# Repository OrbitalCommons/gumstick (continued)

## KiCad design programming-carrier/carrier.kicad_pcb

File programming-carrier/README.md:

# Module v1 programming and lighting test fixture

This is the **ordered programming-carrier v1**, a USB programmer and slow GPIO
indicator fixture for the ESP32-S2 + iCE40 module. Use the [daughterboard ICD](../current-df40-connectors/docs/ICD-v1.md)
for the interface, [design notes](docs/DESIGN.md) for the circuit, and
[ordered snapshot](releases/v1/README.md) for manufacturing files.

The procedure below specifies a test program to implement. There is **no complete
fixture firmware included here**. Affogato supplies build/loading/SPI building
blocks; [these reviewed setup notes](https://github.com/OrbitalCommons/stratumzero/blob/main/boards/stratumzero/docs/integration/affogato.md)
explain its current capabilities and limitations. The calibrator's GPIO assignments
and bitstream must **not** be used as the fixture test mapping.

## What the LEDs show

There are60 monitored interface signals:27ESP signals (including EN and input-only
GPIO46),30regular FPGA I/O and3FPGA RGB sink outputs. D1/D2 are independent5V and
3V3 TEST indicators. The monitor buffers have both /OE pins tied to ground:
**there is no software bank-enable signal**. “One bank at a time” means drive
only that bank's eligible GPIOs active while driving other eligible outputs inactive.

Green signal LEDs indicate HIGH. Red RGB monitor LEDs indicate LOW. Each monitor
has its own resistor and buffer; the GPIO drives a high-impedance input with100k
bias, not the LED current. An LED being lit proves an observed logic level,
not rated drive strength or a complete input-path/analog/high-speed test.

Use [led-map.json](docs/led-map.json) as the machine-readable test list. Group by
`buffer`, preserve `input` order, and carry `active_low`; do not assume consecutive
LED reference numbers cover every footprint or that a GPIO suffix is a FPGA pad.
The [ICD CSV](../current-df40-connectors/docs/icd-v1-pinout.csv) maps each FPGA net to
its physical package pin for the fixture PCF.

## Setup and recovery

1. Unplug USB before fitting/removing the module. Seat both complementary DF40
   connectors evenly and use the2mm spacer/M3 retention without forcing engagement.
2. Connect a data-capable USB cable to an adequately powered, current-limited
   source/hub. This fixture uses USB CC resistors and a500mA-hold fuse; it has
   **no PD negotiation**. Fuse rating is not an authorization to draw arbitrary
   USB current. Start Wi-Fi off and a sparse LED pattern; measure total current.
3. For first flash: SW1=BOOT, press/release SW2 RESET, use native ESP32-S2 USB
   ROM programming, then SW1=RUN and RESET. Release SW3(GPIO46) during reset.
4. Use USB CDC for logs and commands. Disable UART logging/peripherals on43/44
   when testing those pins. Check FPGA loader CDONE and runtime identification.
5. Program distinct firmware identity `programming-carrier-v1-test` and require
   explicit operator arming after boot. This board has no electronic carrier-ID
   interlock: the operator must confirm the fixture. Running this sweep on the
   calibrator would toggle regulator enables, I²C and GPS pins as arbitrary LEDs.

## Pin classes: do not blindly sweep everything

| Signal | Treatment |
|---|---|
| ESP_EN / D10 | Observe high during normal run; SW2 reset tests it. Never use as a normal firmware output |
| GPIO0 / D11 | Keep high/input normally; SW1 controls BOOT/RUN. Exclude from automated bank/walk tests |
| GPIO46 / D36 | **Input only**; use SW3 after boot, read low released/high pressed. Never set output mode |
| GPIO45 / D35 | Flash-voltage strap. Keep low/high-Z through reset; optional separate post-boot test only, then return low before reset |
| ESP GPIO1–8,15–18,21,33–35,38–44 | Ordinary fixture outputs after disabling other peripheral owners |
| ESP GPIO9–14,36,37 | Internal FPGA link/reset/CDONE; not part of indicator sweep |
| ESP GPIO19/20 | USB; never repurpose during USB testing |
| FPGA ordinary30GPIOs | Output test via dedicated FPGA test design, physical pins from ICD |
| FPGA RGB0/1/2 | Current-sink outputs shared with module RGB LED; separate RGB-driver test |

Normal EN and GPIO0 indicators may remain lit while the eligible outputs are
blank. The power indicators also stay on. Log this exception so a technician
does not misdiagnose “all off.” GPIO45's special test should be opt-in; an MCU
reset while a strap is driven high deserves explicit hardware validation.
Do not change eFuses or flash-voltage settings to make a lighting test pass.

## Suggested program structure

- ESP task owns a bank/pin table generated from `led-map.json`, a USB command
  parser, a nonblocking pattern scheduler and a result log.
- A small FPGA fixture image exposes a30-bit regular-output mask, three RGB
  controls, readback/identity and a heartbeat/watchdog. It can use HFOSC; no
  external OCXO is fitted on this carrier.
- Use a tested, versioned SPI transport to apply FPGA masks atomically; do not
  assume Affogato's example register map already implements these controls.
- On boot/fault/timeout: regular test outputs low, RGB current sinks disabled,
  GPIO0 left safe, GPIO45low, GPIO46input. Require explicit `start` to illuminate.
- For RGB, use `SB_RGBA_DRV` with a conservative supported current and individual
  PWM controls. “Off” releases the sink, allowing the fixture100k pull-up to turn
  off its red LED. “On” sinks the line low; both module and monitor response should
  be inspected. Do not drive the shared sink pins as push-pull HIGH outputs.

Pseudocode (conceptual API, not an implemented library):

```text
safe_start()
verify_fpga_abi()
wait_for_operator_fixture_confirmation()

for bank in regular_banks_in_physical_order:
    eligible_outputs_off()                # EN/BOOT indicators are exceptions
    set_bank_mask(bank, eligible_mask)    # only post-boot safe push-pull pins
    wait_nonblocking(1000 ms)
    record_operator_result(bank)
    eligible_outputs_off()
    wait_nonblocking(300 ms)

for bank in regular_banks_in_physical_order:
    for channel in bank.eligible_channels:
        eligible_outputs_off()
        channel_set(channel, ON)
        log_expected_led_and_signal(channel)
        wait_nonblocking(300 ms)
        channel_set(channel, OFF)
        wait_nonblocking(150 ms)

run_checkerboards_one_bank_at_a_time()
run_walking_zero_one_bank_at_a_time()
run_short_all_regular_on_test_if_power_budget_allows()
run_rgb_sink_test_separately()
run_manual_boot_reset_and_gpio46_checks()
eligible_outputs_off()
```

For the human-visible sequence use300–1000ms dwell, not high-frequency PWM.
Offer pause/step/hold/repeat/reverse so a suspect solder joint can be probed.
A camera/photodiode can automate observation later; GPIO register readback alone
cannot confirm that the LED, buffer or connector contact actually works.

## Test phases and expected observations

1. **Baseline:** D1/D2 power, EN and RUN/BOOT indicators as described; all other
   driven regular outputs low and RGB released. Note any stuck-on lamps.
2. **One bank at a time:** light all eligible pins in U3, then U4…U10, with other
   eligible banks off. Verify location, uniformity and no unintended neighboring
   bank. U3/U6 have restricted pins; their whole physical bank will not light.
3. **Walking one:** one eligible green lamp at a time in table order, then reverse.
   Every transition is logged with signal, LED reference, connector and package
   pin. Look for missing, mirrored, duplicated and neighboring lights.
4. **Alternating:** even then odd eligible channels (`0x55` /`0xAA` masked to actual
   channels). Alternate at~2Hz. This can expose shorts masked by an all-on pattern.
5. **Walking zero:** selected bank on except one eligible channel off; other banks
   remain off. This catches stuck-high and pairwise bridge behavior.
6. **Cross-bank/all-on:** brief simultaneous regular-output test after current and
   regulator-temperature checks. The3.3V LDO and USB budget must tolerate it; the
   presence of buffers does not remove the electrical load. Limit dwell initially.
7. **RGB:** individually enable RGB0,RGB1,RGB2 sinks, then combinations. Red monitor
   polarity is inverted; inspect the module RGB LED too. Return all sinks off.
8. **Inputs/control:** press/releaseGPIO46 button after boot and log reads; verify
   EN/reset and BOOT/RUN via the physical controls in a separate controlled step.
9. **Optional input coverage:** place one ordinary pin in input mode, then apply a
   known0/3.3V through a series resistor to its accessible signal-side bias-resistor
   pad; read it back. Never drive against an output or use5V. This is separate from
   the output lamp test and requires deliberate external stimulus.

Proposed USB commands to implement: `fixture status`, `fixture banks`,
`fixture bank U7`, `fixture walk`, `fixture step`, `fixture hold FPGA_IOB_3B_G6`,
`fixture checkerboard`, `fixture rgb 1`, `fixture input46`, `fixture stop`.
`stop` must work during every dwell; use task timers/state transitions, not a
blocking multi-minute loop. Reset should return to idle, never auto-repeat all-on.

## Test report and coverage limits

Save module serial/operator ID, module/interface revision, app/FPGA hashes,
measured USB voltage/current, selected dwell, expected/observed result for each
channel, optional photos and faults. Distinguish **command applied**, **pin readback**,
and **optically observed**; only the last establishes a visible lamp result.

This fixture does not validate RF performance, high-speed signal integrity,
FPGA global clock routing, ADC precision, full current capability or every input
path. It loads signals with long traces/buffer inputs and is intended for slow
functional tests. Finish with outputs safe, SW1 RUN, and OTA/recovery firmware
validated before installing the module on an application carrier.

## Physical bank/channel order

The table below is generated from `docs/led-map.json` for the ordered fixture.
D37–D41 and D72–D73 are not populated channels in this map; do not fill numeric gaps.

| Buffer | Kind | Channels in input-pin order |
|---|---|---|
| U3 | ESP | D10=EN; D11=GPIO0_BOOT; D12=GPIO1; D13=GPIO2; D14=GPIO3; D15=GPIO4; D16=GPIO5; D17=GPIO6 |
| U4 | ESP | D18=GPIO7; D19=GPIO8; D20=GPIO15; D21=GPIO16; D22=GPIO17; D23=GPIO18; D24=GPIO21; D25=GPIO33 |
| U5 | ESP | D26=GPIO34; D27=GPIO35; D28=GPIO38; D29=GPIO39; D30=GPIO40; D31=GPIO41; D32=GPIO42; D33=GPIO43_TXD |
| U6 | ESP | D34=GPIO44_RXD; D35=GPIO45; D36=GPIO46 |
| U7 | FPGA | D42=IOB_0A; D43=IOB_2A; D44=IOB_3B_G6; D45=IOB_4A; D46=IOB_5B; D47=IOB_6A; D48=IOB_8A; D49=IOB_9B |
| U8 | FPGA | D50=IOB_13B; D51=IOB_16A; D52=IOB_18A; D53=IOB_20A; D54=IOB_22A; D55=IOB_23B; D56=IOB_25B_G3; D57=IOB_29B |
| U9 | FPGA | D58=IOT_36B; D59=IOT_37A; D60=IOT_38B; D61=IOT_39A; D62=IOT_41A; D63=IOT_42B; D64=IOT_43A; D65=IOT_44B |
| U10 | FPGA | D66=IOT_45A_G1; D67=IOT_46B_G0; D68=IOT_48B; D69=IOT_49A; D70=IOT_50B; D71=IOT_51A |
| U11 | RGB | D74=RGB0; D75=RGB1; D76=RGB2 |

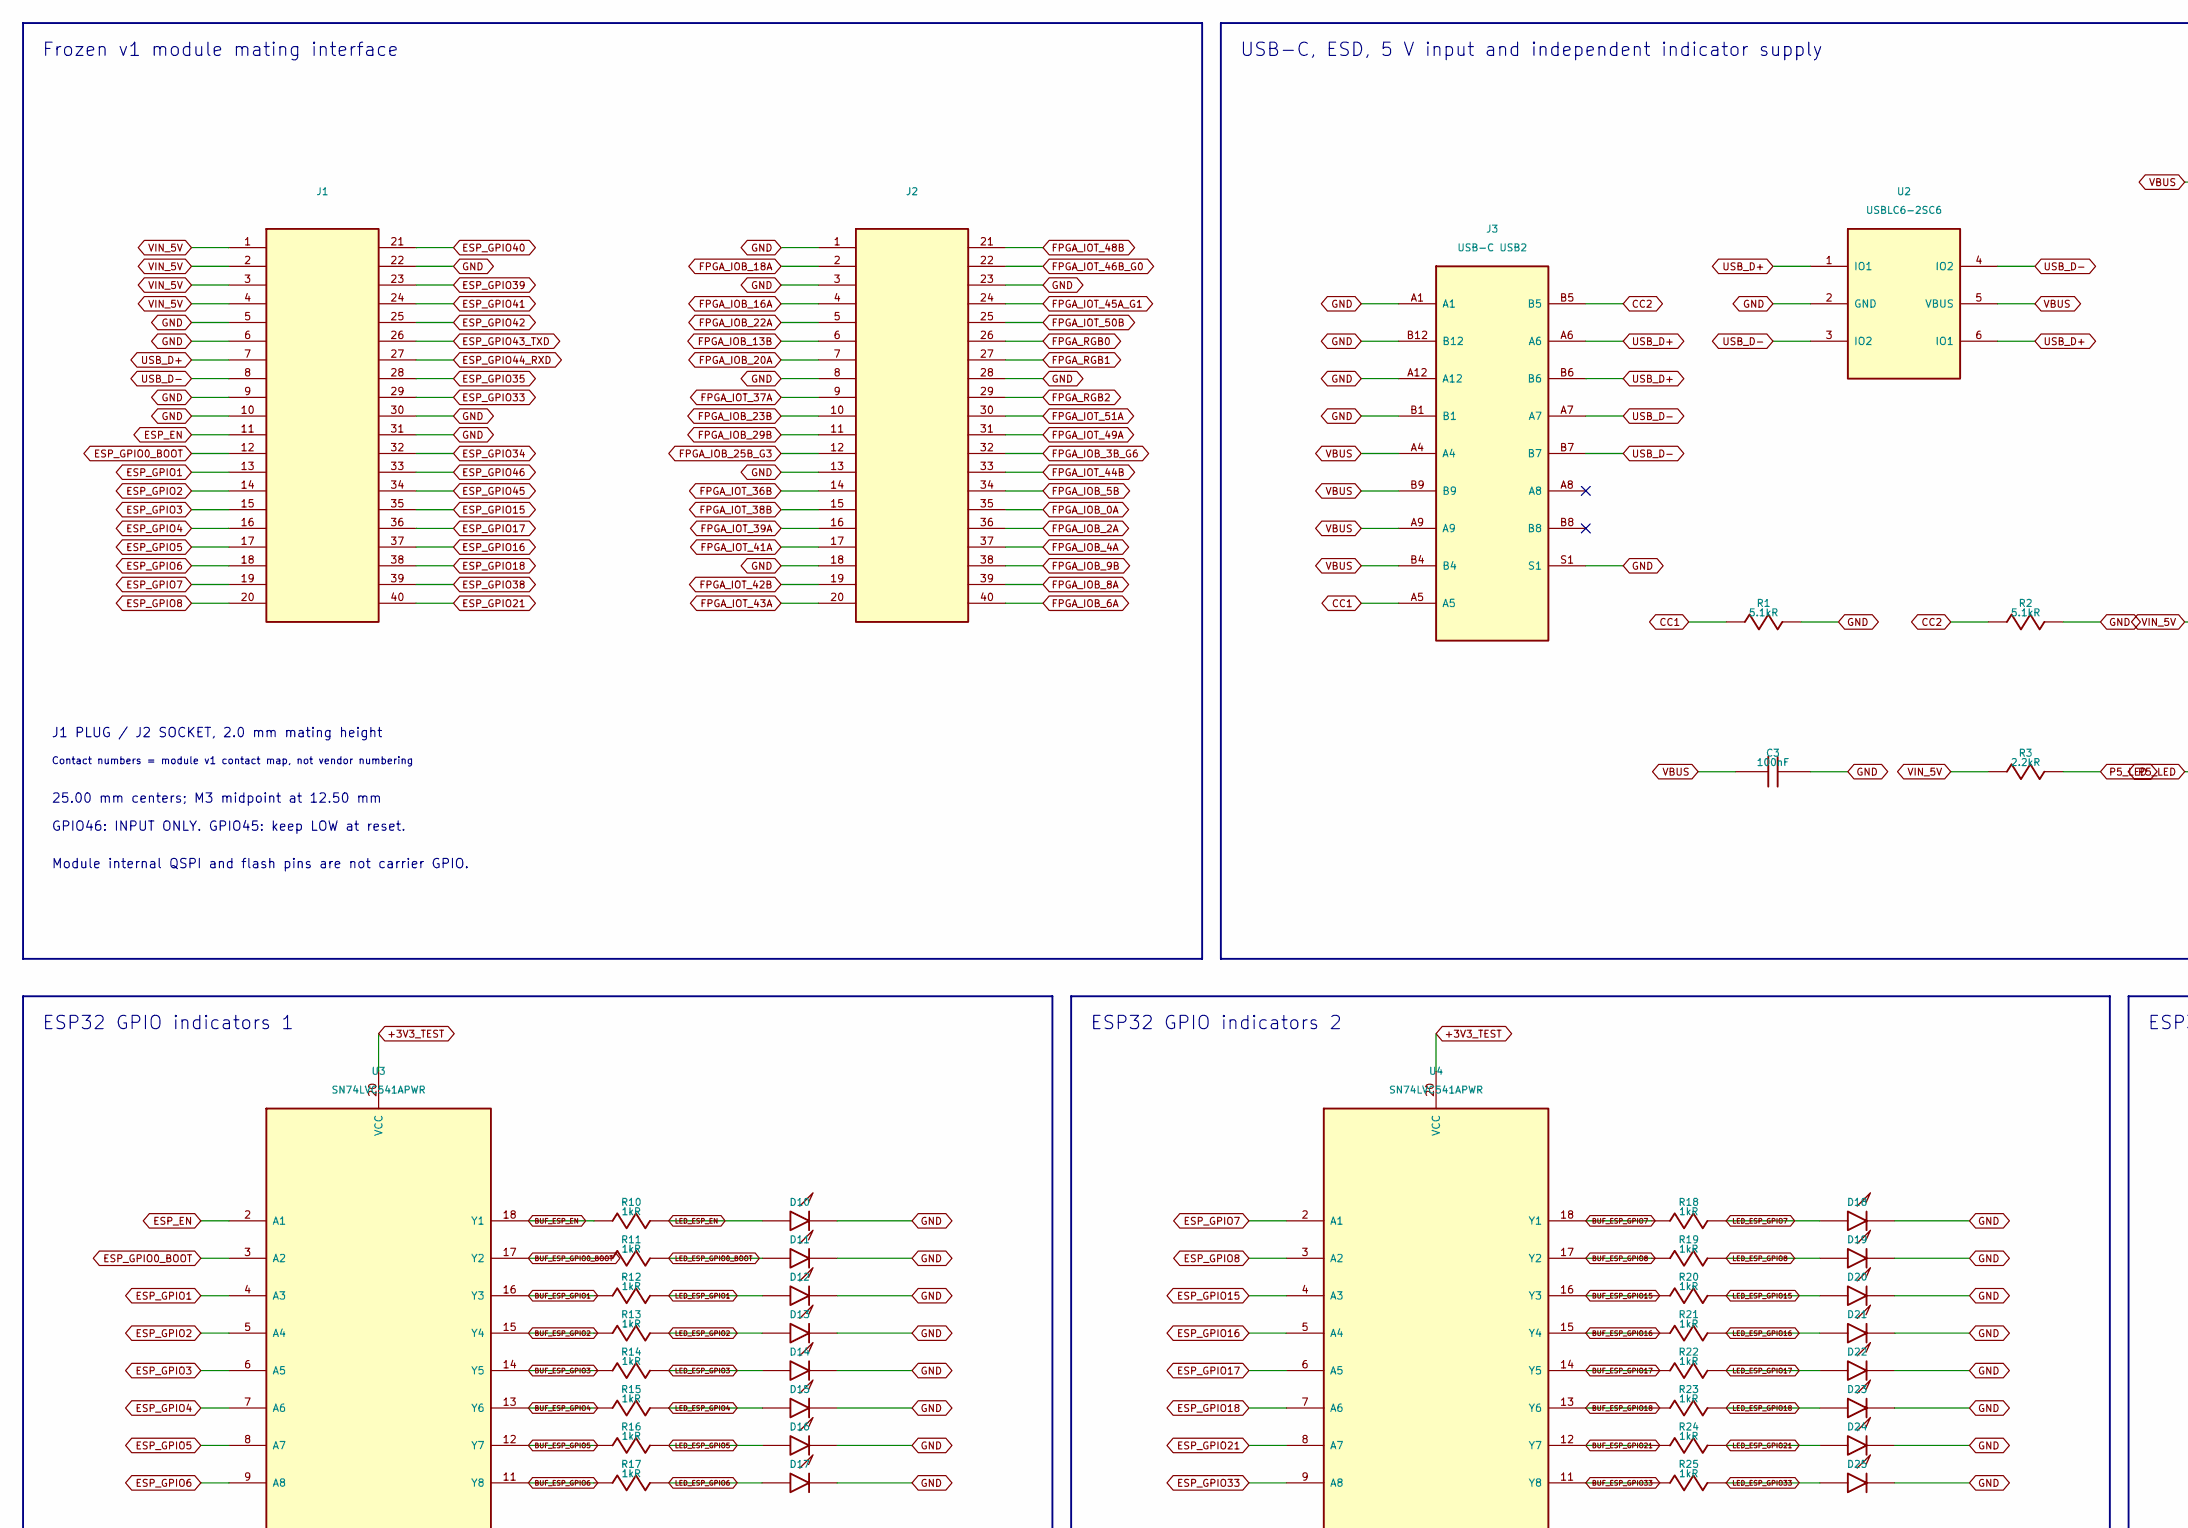
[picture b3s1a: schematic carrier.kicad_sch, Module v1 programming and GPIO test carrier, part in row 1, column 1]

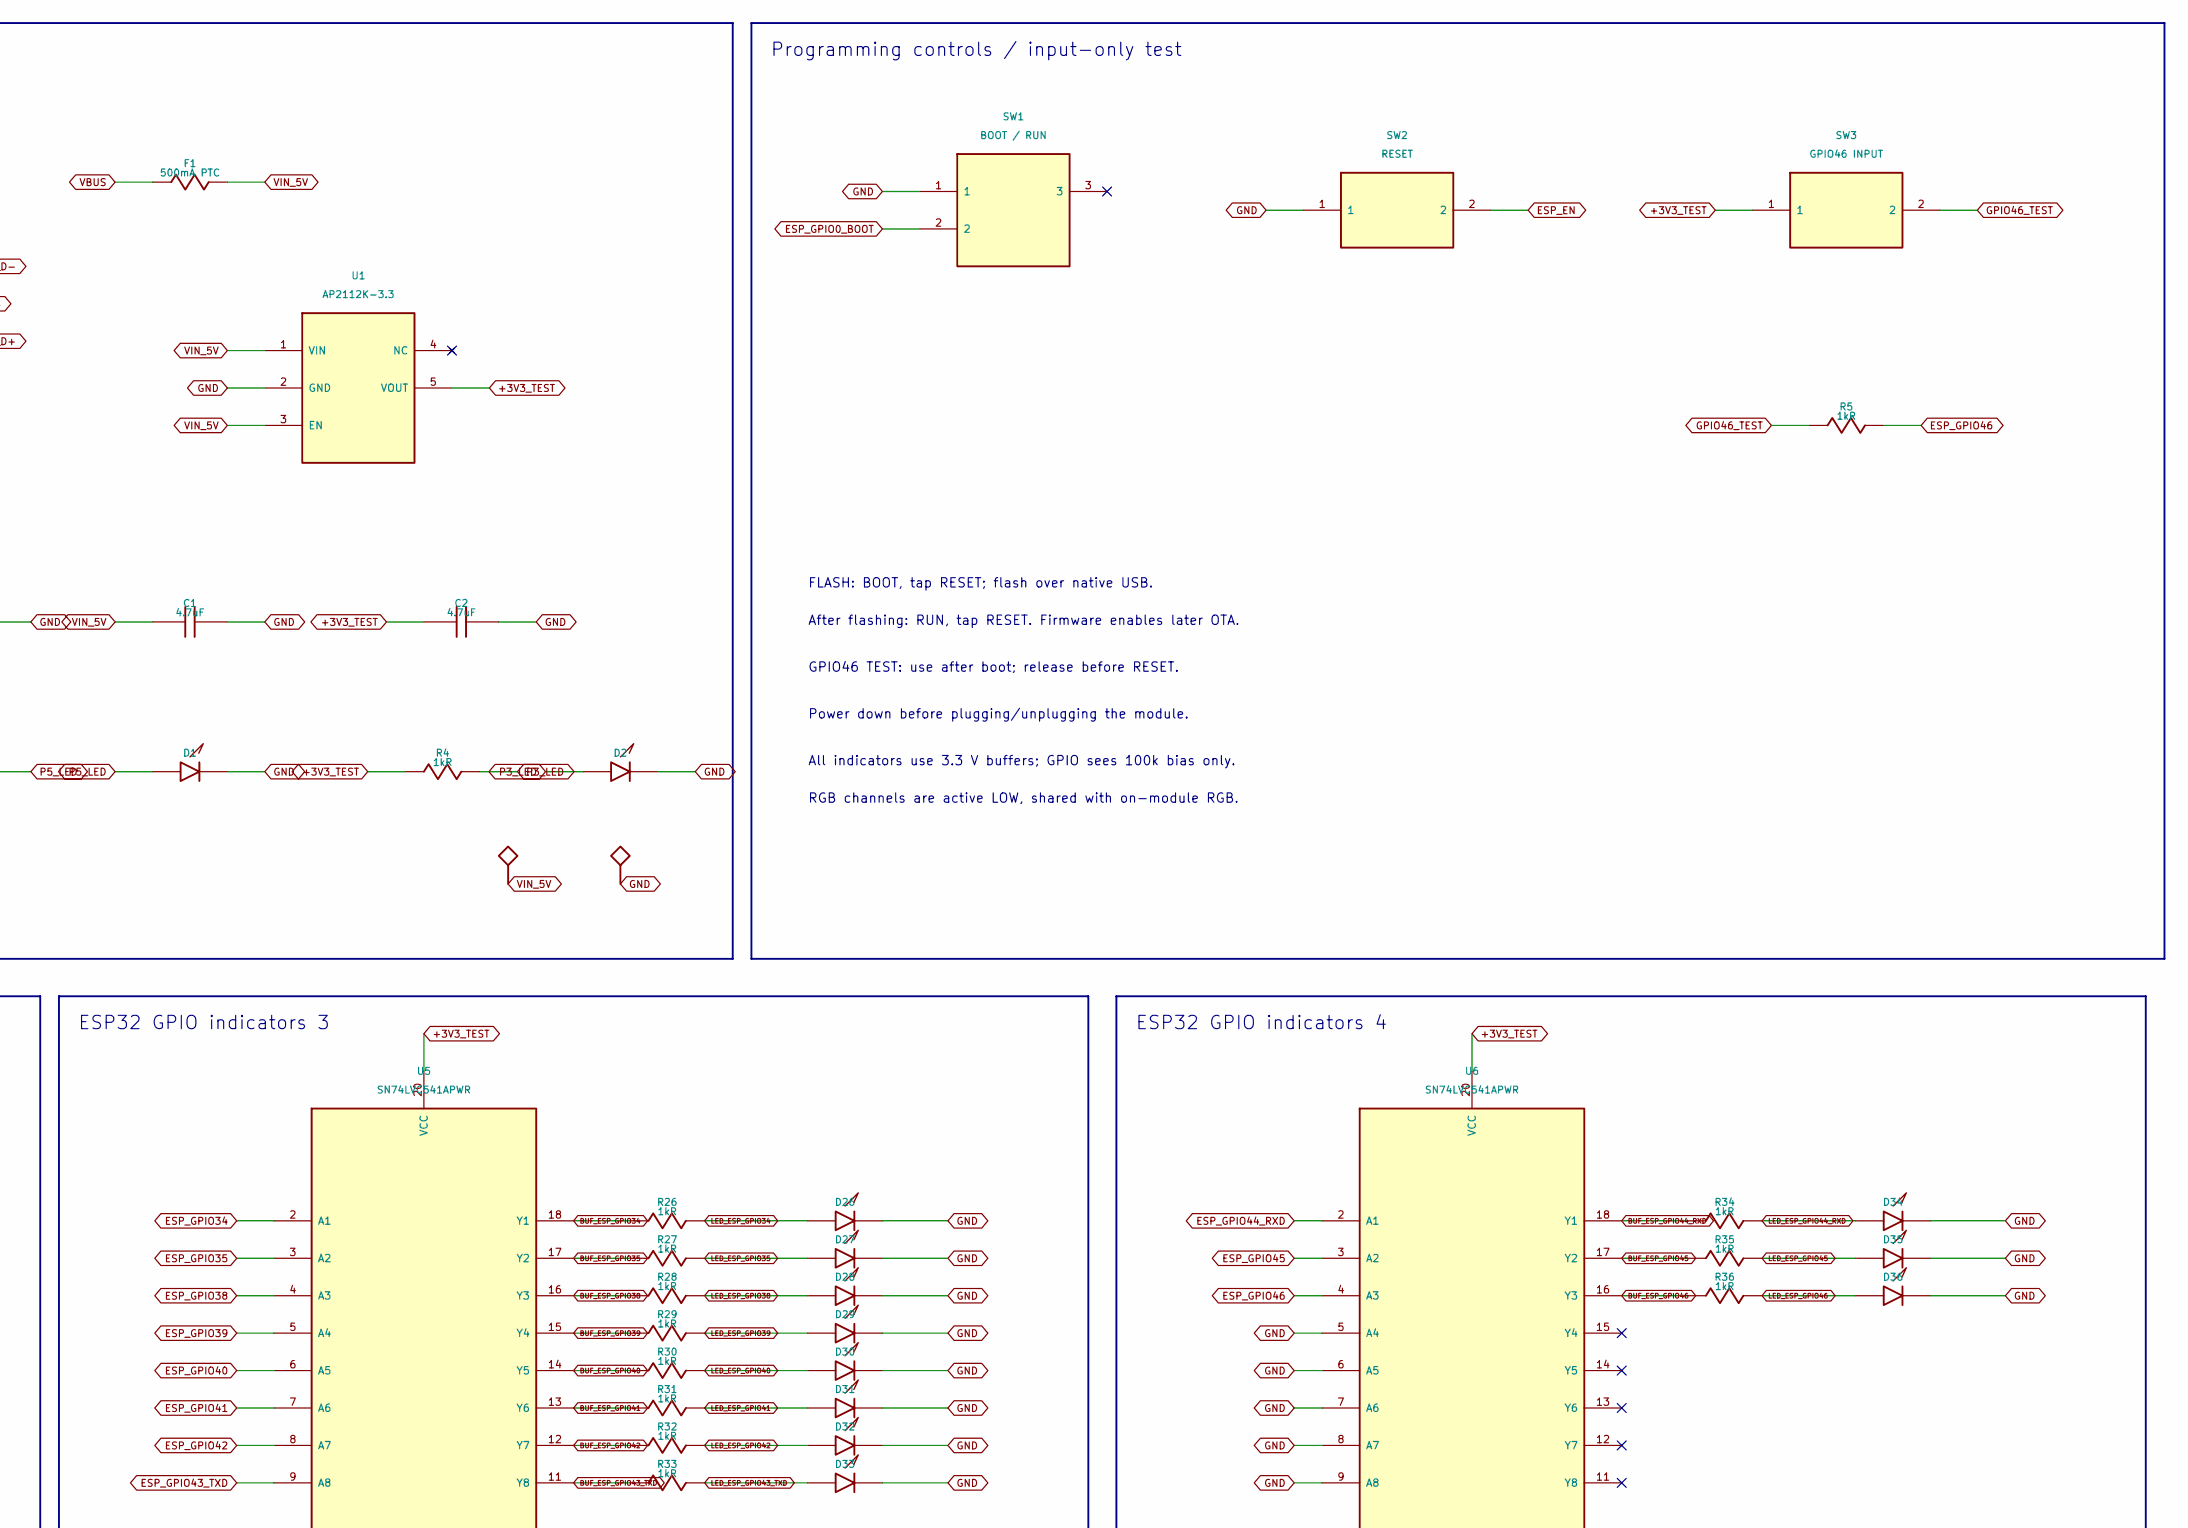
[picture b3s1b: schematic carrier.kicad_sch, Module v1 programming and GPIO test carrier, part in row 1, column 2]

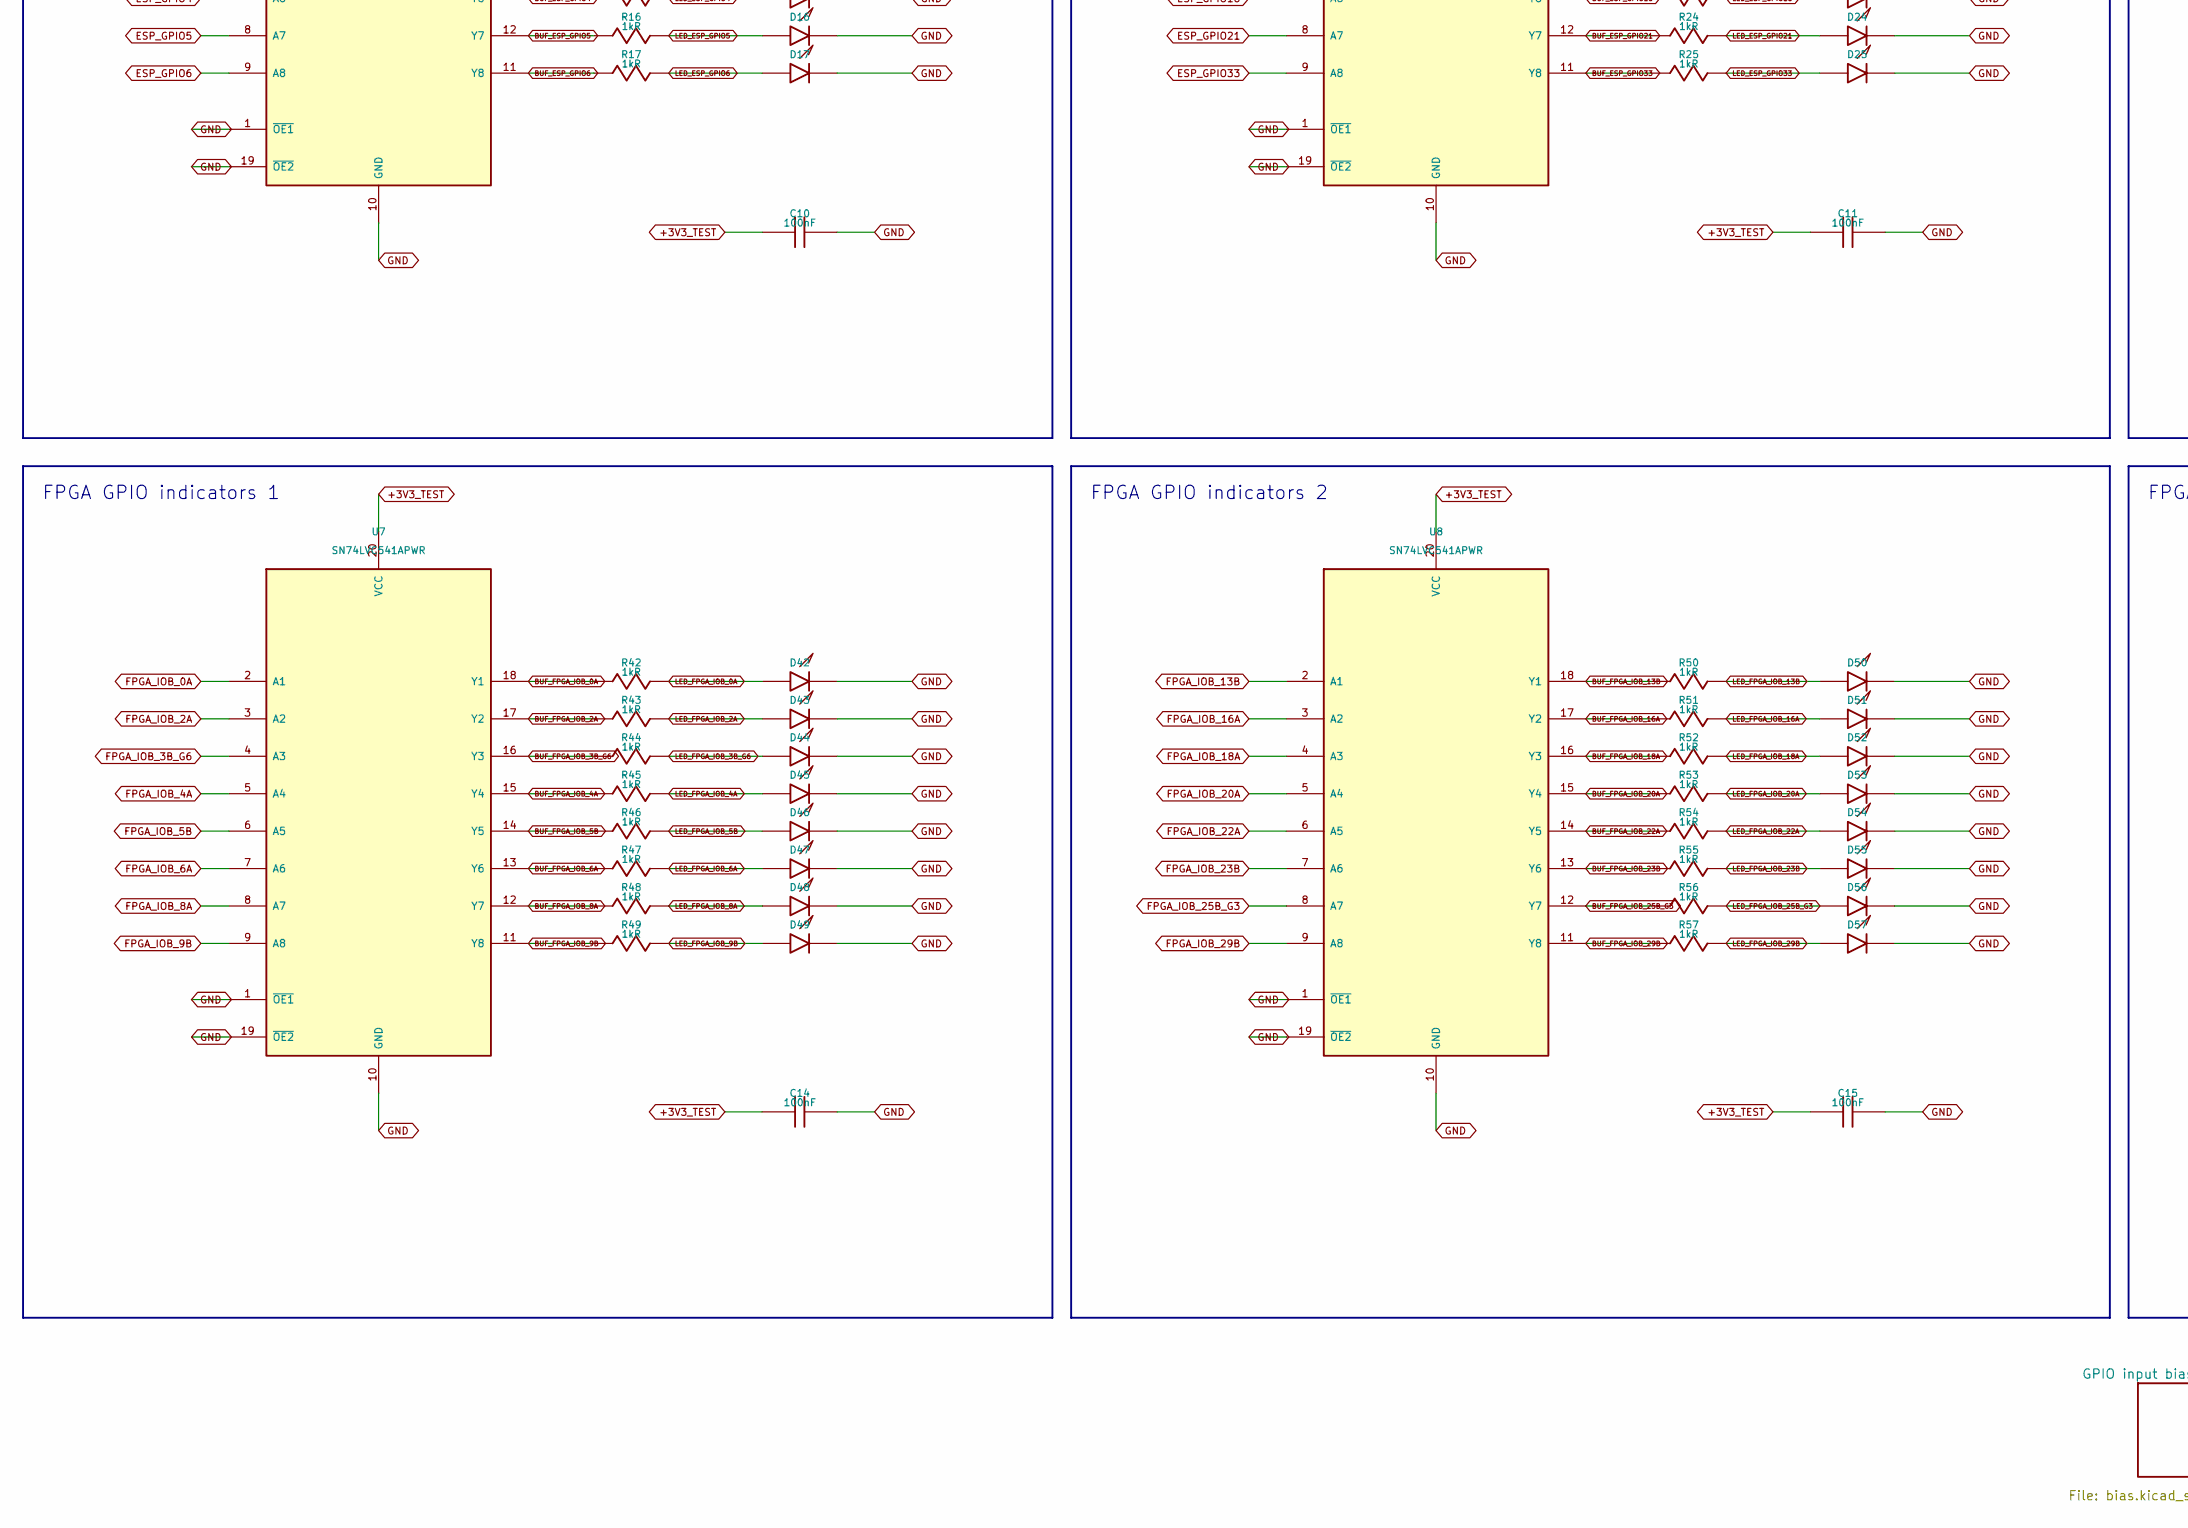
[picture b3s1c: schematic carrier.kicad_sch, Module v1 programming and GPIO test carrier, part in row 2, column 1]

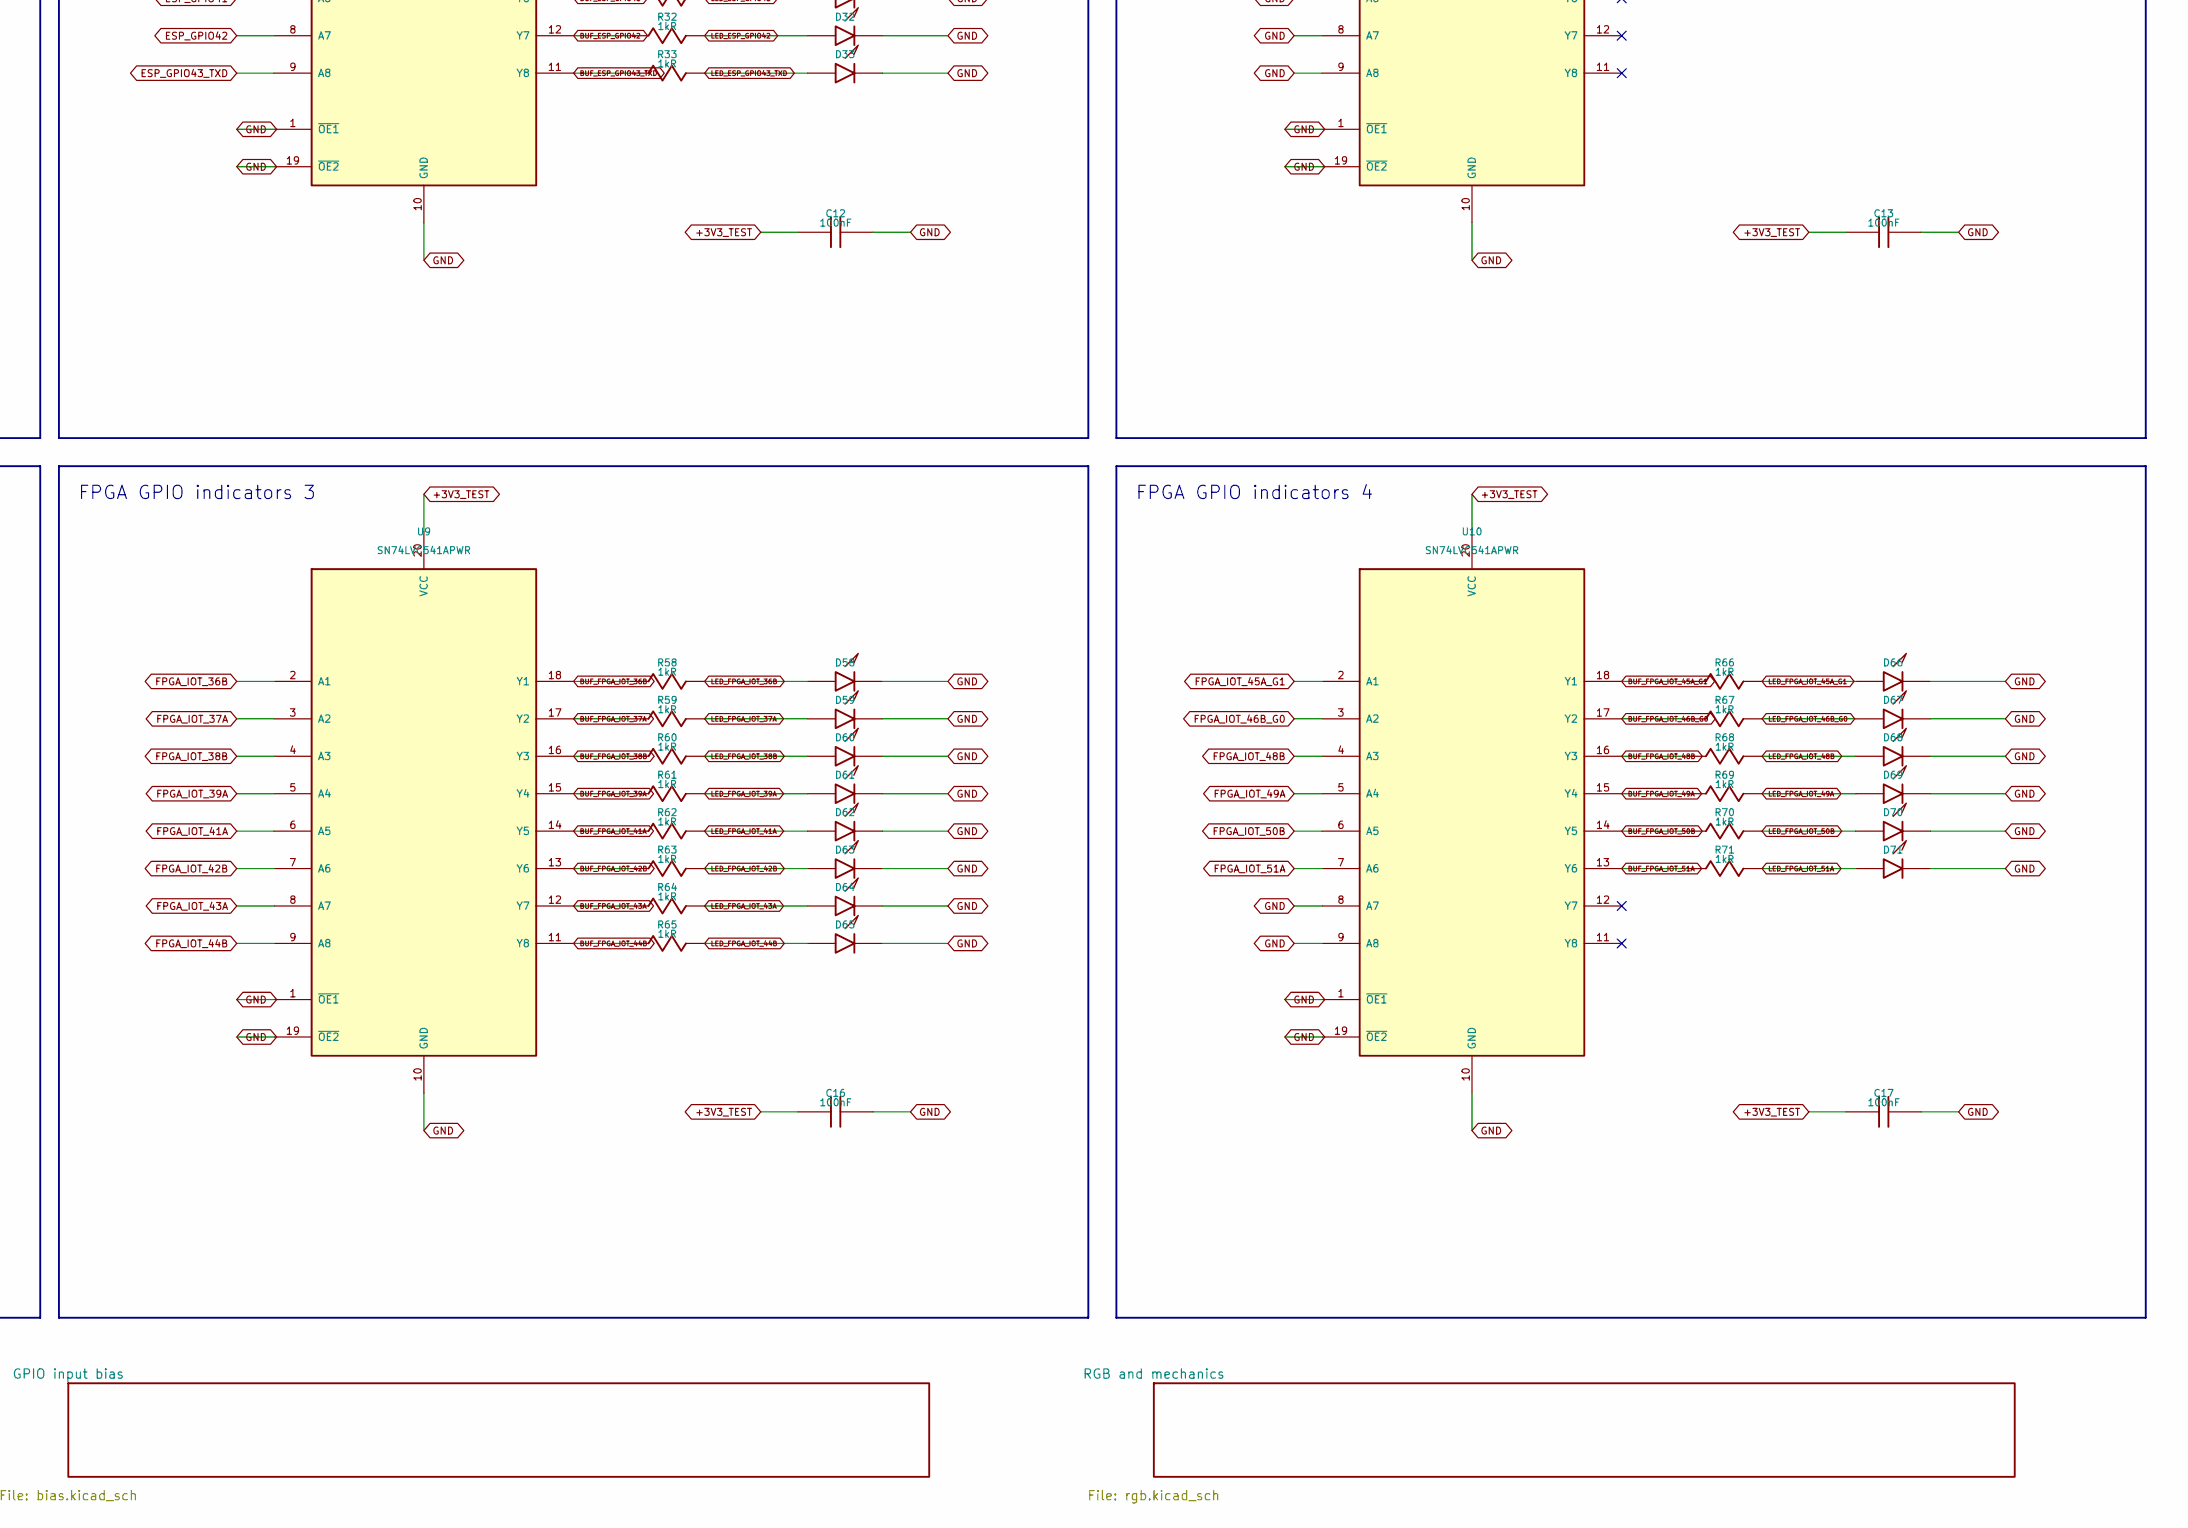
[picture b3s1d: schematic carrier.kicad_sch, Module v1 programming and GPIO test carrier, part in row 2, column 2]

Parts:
C1, C2: 4.7uF; C_0603_1608Metric; MPN CL10A475KO8NNNC; LCSC C19666
C3, C10, C11, C12, C13, C14, C15, C16, C17: 100nF; C_0603_1608Metric; MPN CC0603KRX7R9BB104; LCSC C14663
D1, D2, D10, D11, D12, D13, D14, D15, D16, D17, D18, D19, D20, D21, D22, D23, D24, D25, D26, D27, D28, D29, D30, D31, D32, D33, D34, D35, D36, D42, D43, D44, D45, D46, D47, D48, D49, D50, D51, D52, D53, D54, D55, D56, D57, D58, D59, D60, D61, D62, D63, D64, D65, D66, D67, D68, D69, D70, D71: GREEN; LED_0603_1608Metric; MPN XL-1608SYGC-06; LCSC C965805
F1: 500mA PTC; Fuse_1206_3216Metric; MPN 1206L050/15YR; LCSC C151162
J1: DF40C-40DP-0.4V(51); J1_Module_v1_Mate; MPN DF40C-40DP-0.4V(51); LCSC C424643
J2: DF40C(2.0)-40DS-0.4V(51); J2_Module_v1_Mate; MPN DF40C(2.0)-40DS-0.4V(51); LCSC C597934
J3: USB-C USB2; USB_C_Receptacle_HRO_TYPE-C-31-M-12; MPN TYPE-C-31-M-12; LCSC C165948
R1, R2: 5.1kR; R_0603_1608Metric; MPN 0603WAF5101T5E; LCSC C23186
R3: 2.2kR; R_0603_1608Metric; MPN 0603WAF2201T5E; LCSC C4190
R4, R5, R10, R11, R12, R13, R14, R15, R16, R17, R18, R19, R20, R21, R22, R23, R24, R25, R26, R27, R28, R29, R30, R31, R32, R33, R34, R35, R36, R42, R43, R44, R45, R46, R47, R48, R49, R50, R51, R52, R53, R54, R55, R56, R57, R58, R59, R60, R61, R62, R63, R64, R65, R66, R67, R68, R69, R70, R71: 1kR; R_0603_1608Metric; MPN 0603WAF1001T5E; LCSC C21190
SW1: BOOT / RUN; SW_SPDT_CK_JS102011SAQN; MPN JS102011SAQN; LCSC C221660
SW2: RESET; SW_SPST_TL3342; MPN TL3342F160QG; LCSC C2886898
SW3: GPIO46 INPUT; SW_SPST_TL3342; MPN TL3342F160QG; LCSC C2886898
U1: AP2112K-3.3; SOT-23-5; MPN AP2112K-3.3TRG1; LCSC C51118
U2: USBLC6-2SC6; SOT-23-6; MPN USBLC6-2SC6; LCSC C7519
U3, U4, U5, U6, U7, U8, U9, U10: SN74LVC541APWR; TSSOP-20_4.4x6.5mm_P0.65mm; MPN SN74LVC541APWR; LCSC C113281

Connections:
+3V3_TEST: C2.1, C10.1, C11.1, C12.1, C13.1, C14.1, C15.1, C16.1, C17.1, R4.1, SW3.1, U1.5 (VOUT), U3.20 (VCC), U4.20 (VCC), U5.20 (VCC), U6.20 (VCC), U7.20 (VCC), U8.20 (VCC), U9.20 (VCC), U10.20 (VCC); also elsewhere on the board
BUF_ESP_EN: R10.1, U3.18 (Y1)
BUF_ESP_GPIO0_BOOT: R11.1, U3.17 (Y2)
BUF_ESP_GPIO1: R12.1, U3.16 (Y3)
BUF_ESP_GPIO2: R13.1, U3.15 (Y4)
BUF_ESP_GPIO3: R14.1, U3.14 (Y5)
BUF_ESP_GPIO4: R15.1, U3.13 (Y6)
BUF_ESP_GPIO5: R16.1, U3.12 (Y7)
BUF_ESP_GPIO6: R17.1, U3.11 (Y8)
BUF_ESP_GPIO7: R18.1, U4.18 (Y1)
BUF_ESP_GPIO8: R19.1, U4.17 (Y2)
BUF_ESP_GPIO15: R20.1, U4.16 (Y3)
BUF_ESP_GPIO16: R21.1, U4.15 (Y4)
BUF_ESP_GPIO17: R22.1, U4.14 (Y5)
BUF_ESP_GPIO18: R23.1, U4.13 (Y6)
BUF_ESP_GPIO21: R24.1, U4.12 (Y7)
BUF_ESP_GPIO33: R25.1, U4.11 (Y8)
BUF_ESP_GPIO34: R26.1, U5.18 (Y1)
BUF_ESP_GPIO35: R27.1, U5.17 (Y2)
BUF_ESP_GPIO38: R28.1, U5.16 (Y3)
BUF_ESP_GPIO39: R29.1, U5.15 (Y4)
BUF_ESP_GPIO40: R30.1, U5.14 (Y5)
BUF_ESP_GPIO41: R31.1, U5.13 (Y6)
BUF_ESP_GPIO42: R32.1, U5.12 (Y7)
BUF_ESP_GPIO43_TXD: R33.1, U5.11 (Y8)
BUF_ESP_GPIO44_RXD: R34.1, U6.18 (Y1)
BUF_ESP_GPIO45: R35.1, U6.17 (Y2)
BUF_ESP_GPIO46: R36.1, U6.16 (Y3)
BUF_FPGA_IOB_0A: R42.1, U7.18 (Y1)
BUF_FPGA_IOB_2A: R43.1, U7.17 (Y2)
BUF_FPGA_IOB_3B_G6: R44.1, U7.16 (Y3)
BUF_FPGA_IOB_4A: R45.1, U7.15 (Y4)
BUF_FPGA_IOB_5B: R46.1, U7.14 (Y5)
BUF_FPGA_IOB_6A: R47.1, U7.13 (Y6)
BUF_FPGA_IOB_8A: R48.1, U7.12 (Y7)
BUF_FPGA_IOB_9B: R49.1, U7.11 (Y8)
BUF_FPGA_IOB_13B: R50.1, U8.18 (Y1)
BUF_FPGA_IOB_16A: R51.1, U8.17 (Y2)
BUF_FPGA_IOB_18A: R52.1, U8.16 (Y3)
BUF_FPGA_IOB_20A: R53.1, U8.15 (Y4)
BUF_FPGA_IOB_22A: R54.1, U8.14 (Y5)
BUF_FPGA_IOB_23B: R55.1, U8.13 (Y6)
BUF_FPGA_IOB_25B_G3: R56.1, U8.12 (Y7)
BUF_FPGA_IOB_29B: R57.1, U8.11 (Y8)
BUF_FPGA_IOT_36B: R58.1, U9.18 (Y1)
BUF_FPGA_IOT_37A: R59.1, U9.17 (Y2)
BUF_FPGA_IOT_38B: R60.1, U9.16 (Y3)
BUF_FPGA_IOT_39A: R61.1, U9.15 (Y4)
BUF_FPGA_IOT_41A: R62.1, U9.14 (Y5)
BUF_FPGA_IOT_42B: R63.1, U9.13 (Y6)
BUF_FPGA_IOT_43A: R64.1, U9.12 (Y7)
BUF_FPGA_IOT_44B: R65.1, U9.11 (Y8)
BUF_FPGA_IOT_45A_G1: R66.1, U10.18 (Y1)
BUF_FPGA_IOT_46B_G0: R67.1, U10.17 (Y2)
BUF_FPGA_IOT_48B: R68.1, U10.16 (Y3)
BUF_FPGA_IOT_49A: R69.1, U10.15 (Y4)
BUF_FPGA_IOT_50B: R70.1, U10.14 (Y5)
BUF_FPGA_IOT_51A: R71.1, U10.13 (Y6)
CC1: J3.A5, R1.1
CC2: J3.B5, R2.1
ESP_EN: J1.11, SW2.2, U3.2 (A1); also elsewhere on the board
ESP_GPIO0_BOOT: J1.12, SW1.2, U3.3 (A2); also elsewhere on the board
ESP_GPIO1: J1.13, U3.4 (A3); also elsewhere on the board
ESP_GPIO2: J1.14, U3.5 (A4); also elsewhere on the board
ESP_GPIO3: J1.15, U3.6 (A5); also elsewhere on the board
ESP_GPIO4: J1.16, U3.7 (A6); also elsewhere on the board
ESP_GPIO5: J1.17, U3.8 (A7); also elsewhere on the board
ESP_GPIO6: J1.18, U3.9 (A8); also elsewhere on the board
ESP_GPIO7: J1.19, U4.2 (A1); also elsewhere on the board
ESP_GPIO8: J1.20, U4.3 (A2); also elsewhere on the board
ESP_GPIO15: J1.35, U4.4 (A3); also elsewhere on the board
ESP_GPIO16: J1.37, U4.5 (A4); also elsewhere on the board
ESP_GPIO17: J1.36, U4.6 (A5); also elsewhere on the board
ESP_GPIO18: J1.38, U4.7 (A6); also elsewhere on the board
ESP_GPIO21: J1.40, U4.8 (A7); also elsewhere on the board
ESP_GPIO33: J1.29, U4.9 (A8); also elsewhere on the board
ESP_GPIO34: J1.32, U5.2 (A1); also elsewhere on the board
ESP_GPIO35: J1.28, U5.3 (A2); also elsewhere on the board
ESP_GPIO38: J1.39, U5.4 (A3); also elsewhere on the board
ESP_GPIO39: J1.23, U5.5 (A4); also elsewhere on the board
ESP_GPIO40: J1.21, U5.6 (A5); also elsewhere on the board
ESP_GPIO41: J1.24, U5.7 (A6); also elsewhere on the board
ESP_GPIO42: J1.25, U5.8 (A7); also elsewhere on the board
ESP_GPIO43_TXD: J1.26, U5.9 (A8); also elsewhere on the board
ESP_GPIO44_RXD: J1.27, U6.2 (A1); also elsewhere on the board
ESP_GPIO45: J1.34, U6.3 (A2); also elsewhere on the board
ESP_GPIO46: J1.33, R5.2, U6.4 (A3); also elsewhere on the board
FPGA_IOB_0A: J2.35, U7.2 (A1); also elsewhere on the board
FPGA_IOB_2A: J2.36, U7.3 (A2); also elsewhere on the board
FPGA_IOB_3B_G6: J2.32, U7.4 (A3); also elsewhere on the board
FPGA_IOB_4A: J2.37, U7.5 (A4); also elsewhere on the board
FPGA_IOB_5B: J2.34, U7.6 (A5); also elsewhere on the board
FPGA_IOB_6A: J2.40, U7.7 (A6); also elsewhere on the board
FPGA_IOB_8A: J2.39, U7.8 (A7); also elsewhere on the board
FPGA_IOB_9B: J2.38, U7.9 (A8); also elsewhere on the board
FPGA_IOB_13B: J2.6, U8.2 (A1); also elsewhere on the board
FPGA_IOB_16A: J2.4, U8.3 (A2); also elsewhere on the board
FPGA_IOB_18A: J2.2, U8.4 (A3); also elsewhere on the board
FPGA_IOB_20A: J2.7, U8.5 (A4); also elsewhere on the board
FPGA_IOB_22A: J2.5, U8.6 (A5); also elsewhere on the board
FPGA_IOB_23B: J2.10, U8.7 (A6); also elsewhere on the board
FPGA_IOB_25B_G3: J2.12, U8.8 (A7); also elsewhere on the board
FPGA_IOB_29B: J2.11, U8.9 (A8); also elsewhere on the board
FPGA_IOT_36B: J2.14, U9.2 (A1); also elsewhere on the board
FPGA_IOT_37A: J2.9, U9.3 (A2); also elsewhere on the board
FPGA_IOT_38B: J2.15, U9.4 (A3); also elsewhere on the board
FPGA_IOT_39A: J2.16, U9.5 (A4); also elsewhere on the board
FPGA_IOT_41A: J2.17, U9.6 (A5); also elsewhere on the board
FPGA_IOT_42B: J2.19, U9.7 (A6); also elsewhere on the board
FPGA_IOT_43A: J2.20, U9.8 (A7); also elsewhere on the board
FPGA_IOT_44B: J2.33, U9.9 (A8); also elsewhere on the board
FPGA_IOT_45A_G1: J2.24, U10.2 (A1); also elsewhere on the board
FPGA_IOT_46B_G0: J2.22, U10.3 (A2); also elsewhere on the board
FPGA_IOT_48B: J2.21, U10.4 (A3); also elsewhere on the board
FPGA_IOT_49A: J2.31, U10.5 (A4); also elsewhere on the board
FPGA_IOT_50B: J2.25, U10.6 (A5); also elsewhere on the board
FPGA_IOT_51A: J2.30, U10.7 (A6); also elsewhere on the board
FPGA_RGB0: J2.26; also elsewhere on the board
FPGA_RGB1: J2.27; also elsewhere on the board
FPGA_RGB2: J2.29; also elsewhere on the board
GND: C1.2, C2.2, C3.2, C10.2, C11.2, C12.2, C13.2, C14.2, C15.2, C16.2, C17.2, D1.1, D2.1, D10.1, D11.1, D12.1, D13.1, D14.1, D15.1, D16.1, D17.1, D18.1, D19.1, D20.1, D21.1, D22.1, D23.1, D24.1, D25.1, D26.1, D27.1, D28.1, D29.1, D30.1, D31.1, D32.1, D33.1, D34.1, D35.1, D36.1, D42.1, D43.1, D44.1, D45.1, D46.1, D47.1, D48.1, D49.1, D50.1, D51.1, D52.1, D53.1, D54.1, D55.1, D56.1, D57.1, D58.1, D59.1, D60.1, D61.1, D62.1, D63.1, D64.1, D65.1, D66.1, D67.1, D68.1, D69.1, D70.1, D71.1, J1.5, J1.6, J1.9, J1.10, J1.22, J1.30, J1.31, J2.1, J2.3, J2.8, J2.13, J2.18, J2.23, J2.28, J3.A1, J3.A12, J3.B1, J3.B12, J3.S1, R1.2, R2.2, SW1.1, SW2.1, U1.2 (GND), U2.2 (GND), U3.1 (~OE1), U3.10 (GND), U3.19 (~OE2), U4.1 (~OE1), U4.10 (GND), U4.19 (~OE2), U5.1 (~OE1), U5.10 (GND), U5.19 (~OE2), U6.1 (~OE1), U6.5 (A4), U6.6 (A5), U6.7 (A6), U6.8 (A7), U6.9 (A8), U6.10 (GND), U6.19 (~OE2), U7.1 (~OE1), U7.10 (GND), U7.19 (~OE2), U8.1 (~OE1), U8.10 (GND), U8.19 (~OE2), U9.1 (~OE1), U9.10 (GND), U9.19 (~OE2), U10.1 (~OE1), U10.8 (A7), U10.9 (A8), U10.10 (GND), U10.19 (~OE2); also elsewhere on the board
GPIO46_TEST: R5.1, SW3.2
LED_ESP_EN: D10.2, R10.2
LED_ESP_GPIO0_BOOT: D11.2, R11.2
LED_ESP_GPIO1: D12.2, R12.2
LED_ESP_GPIO2: D13.2, R13.2
LED_ESP_GPIO3: D14.2, R14.2
LED_ESP_GPIO4: D15.2, R15.2
LED_ESP_GPIO5: D16.2, R16.2
LED_ESP_GPIO6: D17.2, R17.2
LED_ESP_GPIO7: D18.2, R18.2
LED_ESP_GPIO8: D19.2, R19.2
LED_ESP_GPIO15: D20.2, R20.2
LED_ESP_GPIO16: D21.2, R21.2
LED_ESP_GPIO17: D22.2, R22.2
LED_ESP_GPIO18: D23.2, R23.2
LED_ESP_GPIO21: D24.2, R24.2
LED_ESP_GPIO33: D25.2, R25.2
LED_ESP_GPIO34: D26.2, R26.2
LED_ESP_GPIO35: D27.2, R27.2
LED_ESP_GPIO38: D28.2, R28.2
LED_ESP_GPIO39: D29.2, R29.2
LED_ESP_GPIO40: D30.2, R30.2
LED_ESP_GPIO41: D31.2, R31.2
LED_ESP_GPIO42: D32.2, R32.2
LED_ESP_GPIO43_TXD: D33.2, R33.2
LED_ESP_GPIO44_RXD: D34.2, R34.2
LED_ESP_GPIO45: D35.2, R35.2
LED_ESP_GPIO46: D36.2, R36.2
LED_FPGA_IOB_0A: D42.2, R42.2
LED_FPGA_IOB_2A: D43.2, R43.2
LED_FPGA_IOB_3B_G6: D44.2, R44.2
LED_FPGA_IOB_4A: D45.2, R45.2
LED_FPGA_IOB_5B: D46.2, R46.2
LED_FPGA_IOB_6A: D47.2, R47.2
LED_FPGA_IOB_8A: D48.2, R48.2
LED_FPGA_IOB_9B: D49.2, R49.2
LED_FPGA_IOB_13B: D50.2, R50.2
LED_FPGA_IOB_16A: D51.2, R51.2
LED_FPGA_IOB_18A: D52.2, R52.2
LED_FPGA_IOB_20A: D53.2, R53.2
LED_FPGA_IOB_22A: D54.2, R54.2
LED_FPGA_IOB_23B: D55.2, R55.2
LED_FPGA_IOB_25B_G3: D56.2, R56.2
LED_FPGA_IOB_29B: D57.2, R57.2
LED_FPGA_IOT_36B: D58.2, R58.2
LED_FPGA_IOT_37A: D59.2, R59.2
LED_FPGA_IOT_38B: D60.2, R60.2
LED_FPGA_IOT_39A: D61.2, R61.2
LED_FPGA_IOT_41A: D62.2, R62.2
LED_FPGA_IOT_42B: D63.2, R63.2
LED_FPGA_IOT_43A: D64.2, R64.2
LED_FPGA_IOT_44B: D65.2, R65.2
LED_FPGA_IOT_45A_G1: D66.2, R66.2
LED_FPGA_IOT_46B_G0: D67.2, R67.2
LED_FPGA_IOT_48B: D68.2, R68.2
LED_FPGA_IOT_49A: D69.2, R69.2
LED_FPGA_IOT_50B: D70.2, R70.2
LED_FPGA_IOT_51A: D71.2, R71.2
P3_LED: D2.2, R4.2
P5_LED: D1.2, R3.2
USB_D+: J1.7, J3.A6, J3.B6, U2.1 (IO1), U2.6 (IO1)
USB_D-: J1.8, J3.A7, J3.B7, U2.3 (IO2), U2.4 (IO2)
VBUS: C3.1, F1.1, J3.A4, J3.A9, J3.B4, J3.B9, U2.5 (VBUS)
VIN_5V: C1.1, F1.2, J1.1, J1.2, J1.3, J1.4, R3.1, U1.1 (VIN), U1.3 (EN)

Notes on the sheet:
Frozen v1 module mating interface
J1 PLUG / J2 SOCKET, 2.0 mm mating height
Contact numbers = module v1 contact map, not vendor numbering
25.00 mm centers; M3 midpoint at 12.50 mm
GPIO46: INPUT ONLY. GPIO45: keep LOW at reset.
Module internal QSPI and flash pins are not carrier GPIO.
USB-C, ESD, 5 V input and independent indicator supply
Programming controls / input-only test
FLASH: BOOT, tap RESET; flash over native USB.
After flashing: RUN, tap RESET. Firmware enables later OTA.
GPIO46 TEST: use after boot; release before RESET.
Power down before plugging/unplugging the module.
All indicators use 3.3 V buffers; GPIO sees 100k bias only.
RGB channels are active LOW, shared with on-module RGB.
ESP32 GPIO indicators 1
ESP32 GPIO indicators 2
ESP32 GPIO indicators 3
ESP32 GPIO indicators 4
FPGA GPIO indicators 1
FPGA GPIO indicators 2
FPGA GPIO indicators 3
FPGA GPIO indicators 4
